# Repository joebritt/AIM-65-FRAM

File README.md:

# AIM-65-FRAM

Nonvolatile FRAM memory replacement for 2332 ROM used by the Rockwell AIM-65.

<a href="https://oshpark.com/shared_projects/X4W64rqJ"></img></a>

This board plugs into any of the 5 2332 AIM-65 ROM sockets. 
A lead to the 6502 R/W signal is needed for writing to the FRAM.

A Write Protect switch allows disconnecting the R/W signal so that the FRAM truly behaves like a ROM.

The FRAM is 8KB, and the 2332 is only 4KB. A switch selects whether A12 is pulled high or low, giving 2 banks of 4KB. 
A12 may also be tied to an I/O pin, such as from one of the 6522s, to allow programmatic bank selection.

While the memory is true read/write, the Single Step circuitry on the AIM-65 requires A15, A14, and A13 to all be LOW.
As a result, you can't single-step through code in this memory.

Not directly related, but I also had to make new LED display supports for my AIM-65. A tested (in use now!)
3D-printable design can be found 
<a href="https://cad.onshape.com/documents/efebfeba35798ffd247abe96/w/842ecc41860fff750f9e59dd/e/60049825f7dbb6890abf0c50">here.</a>

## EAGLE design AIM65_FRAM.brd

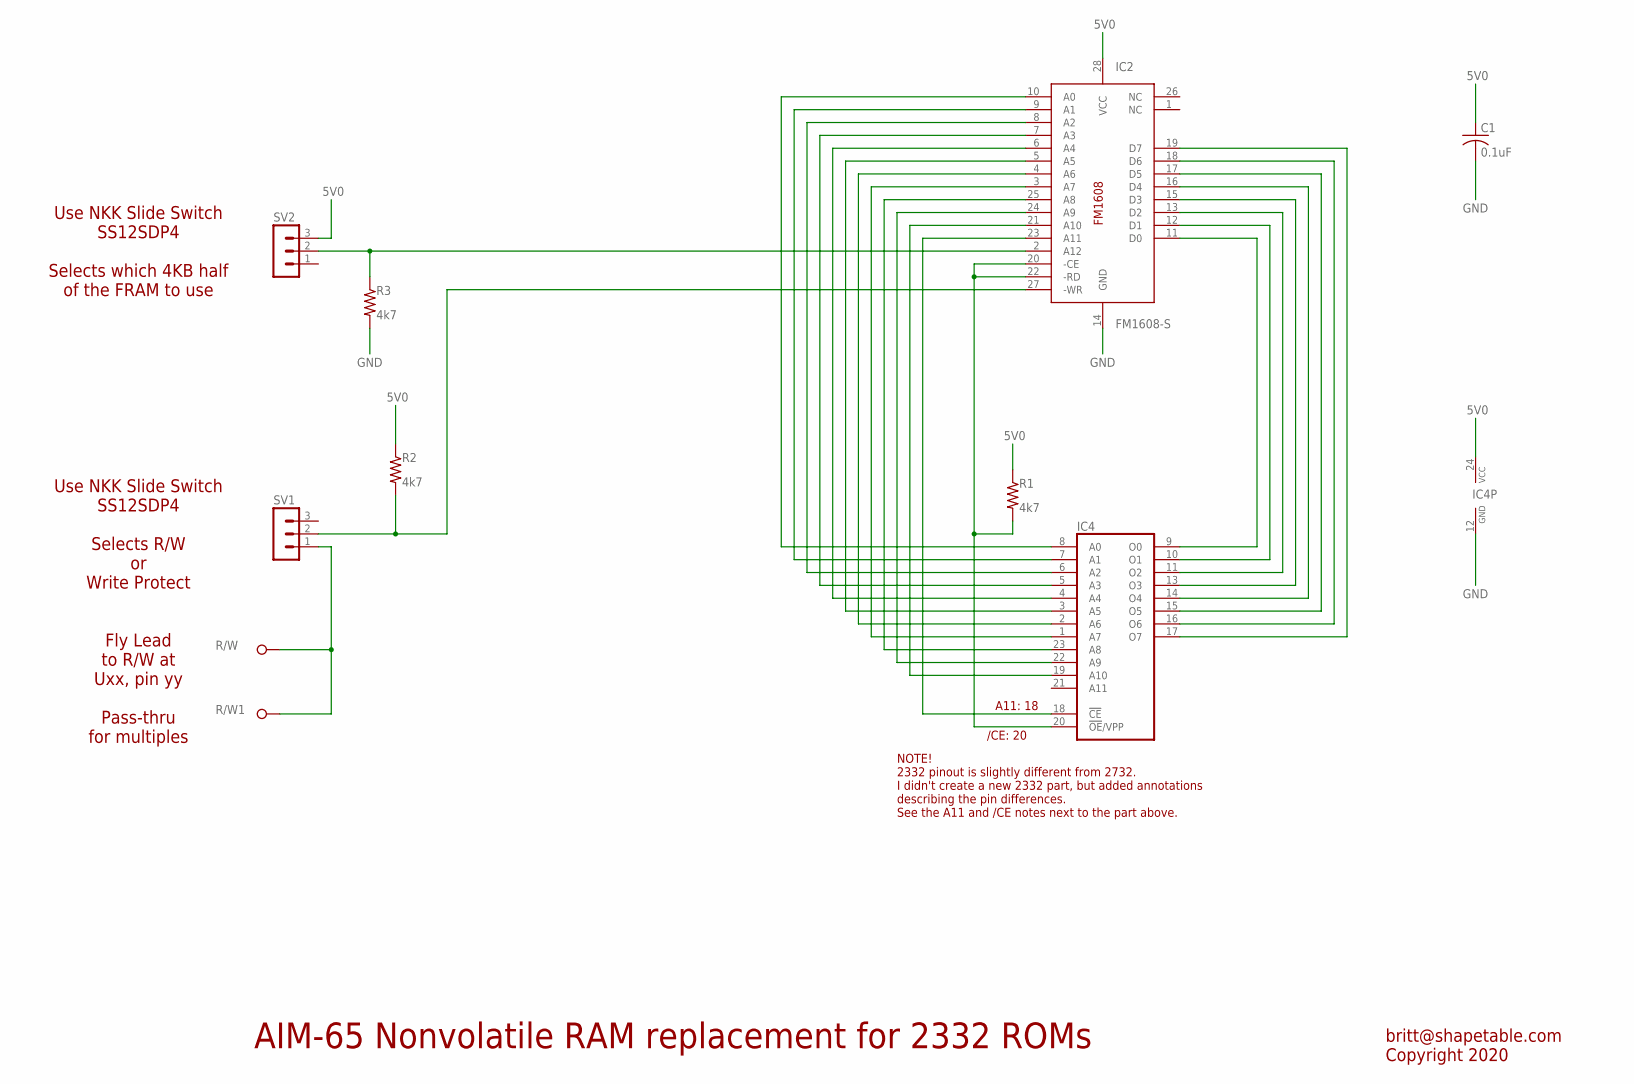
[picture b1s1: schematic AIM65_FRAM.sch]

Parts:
C1: 0.1uF; C0603K
IC2: FM1608-S; SO-28W
IC4: 2732; DIL24
R1, R2, R3: 4k7; R0603
R/W, R/W1: JOE-TP-BIG; JOE-TP-PKG-BIG
SV1, SV2: MA03-1

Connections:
5V0: C1.1, IC2.28 (VCC), IC4.24 (VCC), R1.1, R2.1, SV2.3
GND: C1.2, IC2.14 (GND), IC4.12 (GND), R3.2
unnamed: IC2.10 (A0), IC4.8 (A0)
unnamed: IC2.9 (A1), IC4.7 (A1)
unnamed: IC2.8 (A2), IC4.6 (A2)
unnamed: IC2.7 (A3), IC4.5 (A3)
unnamed: IC2.6 (A4), IC4.4 (A4)
unnamed: IC2.5 (A5), IC4.3 (A5)
unnamed: IC2.4 (A6), IC4.2 (A6)
unnamed: IC2.3 (A7), IC4.1 (A7)
unnamed: IC2.25 (A8), IC4.23 (A8)
unnamed: IC2.24 (A9), IC4.22 (A9)
unnamed: IC2.21 (A10), IC4.19 (A10)
unnamed: IC2.23 (A11), IC4.18 (!CE)
unnamed: IC2.2 (A12), R3.1, SV2.2
unnamed: R/W.1, R/W1.1, SV1.1
unnamed: IC2.20 (-CE), IC2.22 (-RD), IC4.20 (!OE!/VPP), R1.2
unnamed: IC2.27 (-WR), R2.2, SV1.2
unnamed: IC2.19 (D7), IC4.17 (O7)
unnamed: IC2.18 (D6), IC4.16 (O6)
unnamed: IC2.17 (D5), IC4.15 (O5)
unnamed: IC2.16 (D4), IC4.14 (O4)
unnamed: IC2.15 (D3), IC4.13 (O3)
unnamed: IC2.13 (D2), IC4.11 (O2)
unnamed: IC2.12 (D1), IC4.10 (O1)
unnamed: IC2.11 (D0), IC4.9 (O0)

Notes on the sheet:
Use NKK Slide Switch SS12SDP4 Selects which 4KB half of the FRAM to use
Fly Lead to R/W at Uxx, pin yy Pass-thru for multiples
Use NKK Slide Switch SS12SDP4 Selects R/W or Write Protect
A11: 18
/CE: 20
NOTE! 2332 pinout is slightly different from 2732. I didn't create a new 2332 part, but added annotations describing the pin differences. See the A11 and /CE notes next to the part above.
AIM-65 Nonvolatile RAM replacement for 2332 ROMs
britt@shapetable.com Copyright 2020

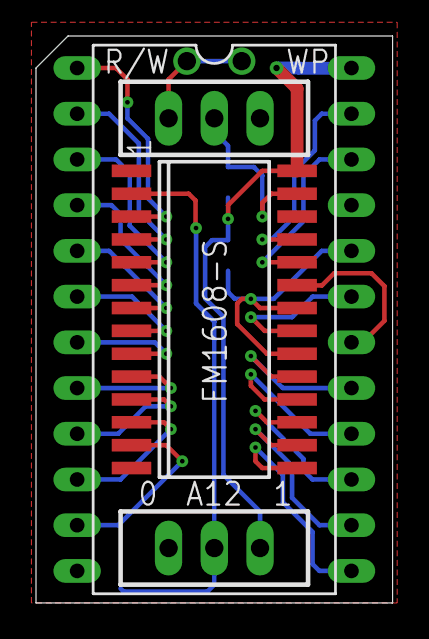
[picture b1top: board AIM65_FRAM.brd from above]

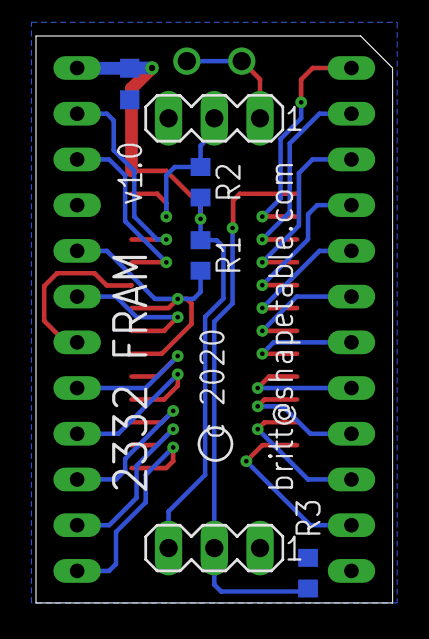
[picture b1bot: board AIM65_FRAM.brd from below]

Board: 2 copper layers, 19.8 x 31.5 mm, 10 parts (6 on the bottom side), 26 nets.

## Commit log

2020-11-02 Add files via upload
    Eagle schematic and board files
    PDFs of schematic, top and bottom layers
